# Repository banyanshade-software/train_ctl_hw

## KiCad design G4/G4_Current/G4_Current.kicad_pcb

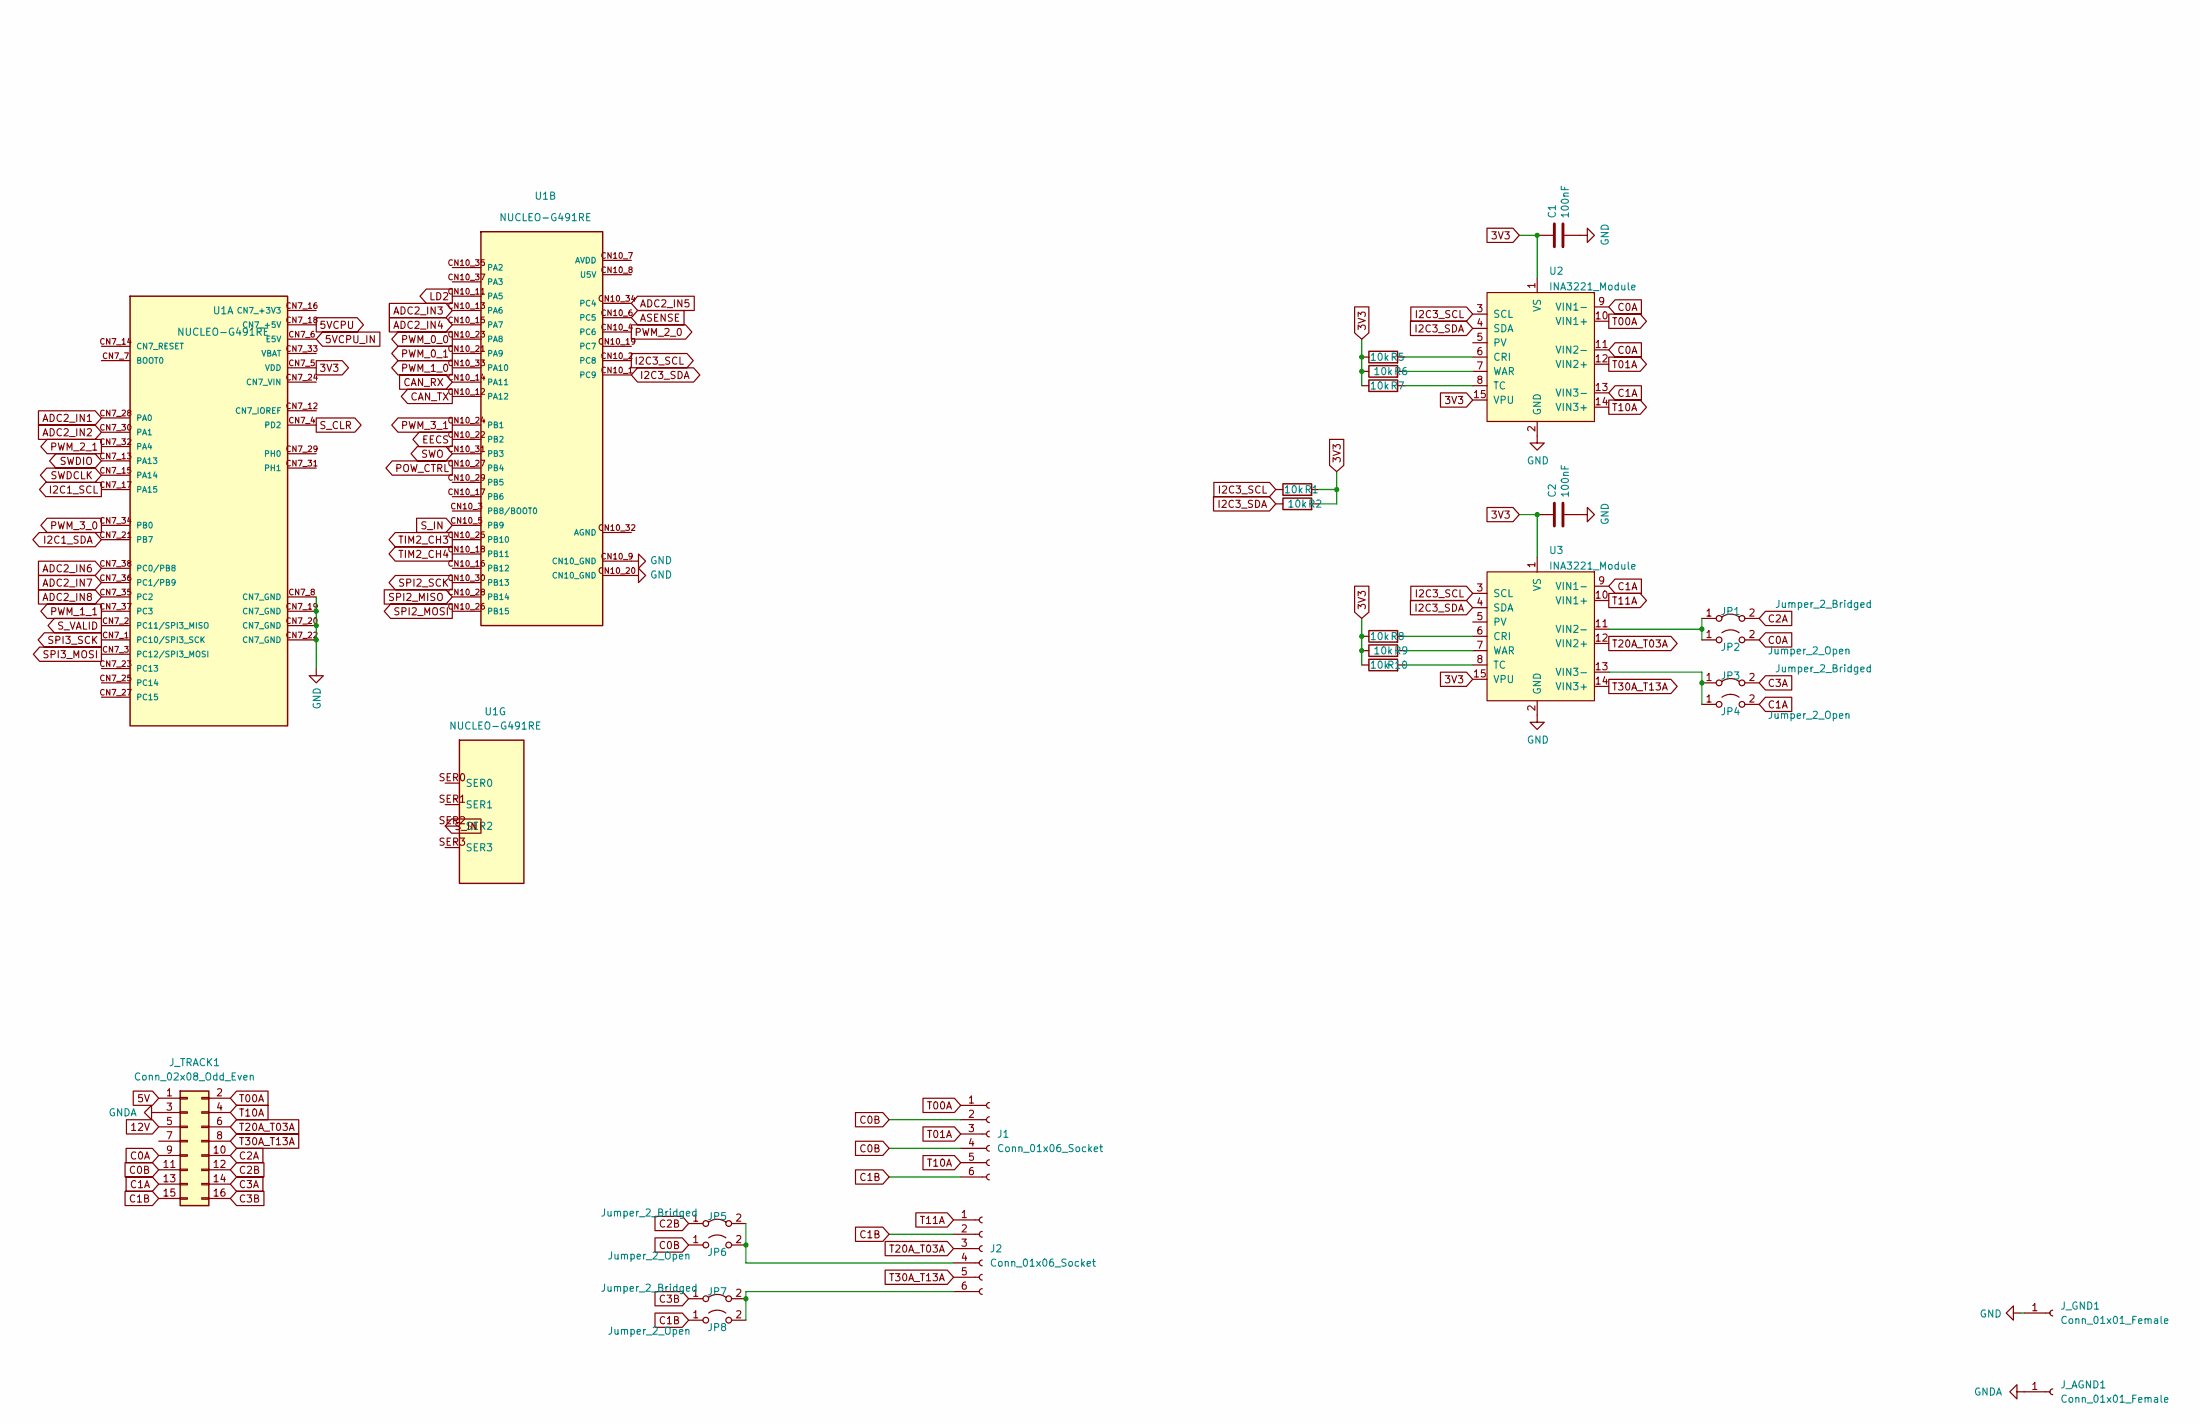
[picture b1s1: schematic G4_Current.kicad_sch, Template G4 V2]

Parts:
C1, C2: 100nF; C_Disc_D3.4mm_W2.1mm_P2.50mm
J1, J2: Conn_01x06_Socket; PinHeader_1x06_P2.54mm_Vertical
JP1, JP3, JP5, JP7: Jumper_2_Bridged; PinHeader_1x02_P2.54mm_Vertical
JP2, JP4, JP6, JP8: Jumper_2_Open; PinHeader_1x02_P2.54mm_Vertical
J_AGND1: Conn_01x01_Female; PinHeader_1x01_P2.54mm_Vertical
J_GND1: Conn_01x01_Female; PinHeader_1x01_P2.54mm_Vertical
J_TRACK1: Conn_02x08_Odd_Even; PinHeader_2x08_P2.54mm_Vertical
R1, R2, R5, R6, R7, R8, R9, R10: 10k; R_Axial_DIN0207_L6.3mm_D2.5mm_P7.62mm_Horizontal
U1: NUCLEO-G491RE; MODULE_NUCLEO-G491RE20noar; PARTREV 13
U2, U3: INA3221_Module

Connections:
3V3: C1.2, C2.2, R1.2, R2.2, R5.1, R6.1, R7.1, R8.1, R9.1, R10.1, U1.CN7_5 (VDD), U2.1 (VS), U2.15 (VPU), U3.1 (VS), U3.15 (VPU)
5V: J_TRACK1.1
5VCPU: U1.CN7_18 (CN7_+5V)
5VCPU_IN: U1.CN7_6 (E5V)
12V: J_TRACK1.5
ADC2_IN1: U1.CN7_28 (PA0)
ADC2_IN2: U1.CN7_30 (PA1)
ADC2_IN3: U1.CN10_13 (PA6)
ADC2_IN4: U1.CN10_15 (PA7)
ADC2_IN5: U1.CN10_34 (PC4)
ADC2_IN6: U1.CN7_38 (PC0/PB8)
ADC2_IN7: U1.CN7_36 (PC1/PB9)
ADC2_IN8: U1.CN7_35 (PC2)
ASENSE: U1.CN10_6 (PC5)
C0A: JP2.2 (B), J_TRACK1.9, U2.9 (VIN1-), U2.11 (VIN2-)
C0B: J1.2, J1.4, JP6.1 (A), J_TRACK1.11
C1A: JP4.2 (B), J_TRACK1.13, U2.13 (VIN3-), U3.9 (VIN1-)
C1B: J1.6, J2.2, JP8.1 (A), J_TRACK1.15
C2A: JP1.2 (B), J_TRACK1.10
C2B: JP5.1 (A), J_TRACK1.12
C3A: JP3.2 (B), J_TRACK1.14
C3B: JP7.1 (A), J_TRACK1.16
CAN_RX: U1.CN10_14 (PA11)
CAN_TX: U1.CN10_12 (PA12)
EECS: U1.CN10_22 (PB2)
GND: C1.1, C2.1, J_GND1.1, U1.CN7_8 (CN7_GND), U1.CN7_19 (CN7_GND), U1.CN7_20 (CN7_GND), U1.CN7_22 (CN7_GND), U1.CN10_9 (CN10_GND), U1.CN10_20 (CN10_GND), U2.2 (GND), U3.2 (GND)
GNDA: J_AGND1.1, J_TRACK1.3
I2C1_SCL: U1.CN7_17 (PA15)
I2C1_SDA: U1.CN7_21 (PB7)
I2C3_SCL: R1.1, U1.CN10_2 (PC8), U2.3 (SCL), U3.3 (SCL)
I2C3_SDA: R2.1, U1.CN10_1 (PC9), U2.4 (SDA), U3.4 (SDA)
LD2: U1.CN10_11 (PA5)
unnamed: J2.4, JP5.2 (B), JP6.2 (B)
unnamed: J2.6, JP7.2 (B), JP8.2 (B)
unnamed: JP1.1 (A), JP2.1 (A), U3.11 (VIN2-)
unnamed: JP3.1 (A), JP4.1 (A), U3.13 (VIN3-)
unnamed: R5.2, U2.6 (CRI)
unnamed: R7.2, U2.8 (TC)
unnamed: R6.2, U2.7 (WAR)
unnamed: R8.2, U3.6 (CRI)
unnamed: R10.2, U3.8 (TC)
unnamed: R9.2, U3.7 (WAR)
POW_CTRL: U1.CN10_27 (PB4)
PWM_0_0: U1.CN10_23 (PA8)
PWM_0_1: U1.CN10_21 (PA9)
PWM_1_0: U1.CN10_33 (PA10)
PWM_1_1: U1.CN7_37 (PC3)
PWM_2_0: U1.CN10_4 (PC6)
PWM_2_1: U1.CN7_32 (PA4)
PWM_3_0: U1.CN7_34 (PB0)
PWM_3_1: U1.CN10_24 (PB1)
SPI2_MISO: U1.CN10_28 (PB14)
SPI2_MOSI: U1.CN10_26 (PB15)
SPI2_SCK: U1.CN10_30 (PB13)
SPI3_MOSI: U1.CN7_3 (PC12/SPI3_MOSI)
SPI3_SCK: U1.CN7_1 (PC10/SPI3_SCK)
SWDCLK: U1.CN7_15 (PA14)
SWDIO: U1.CN7_13 (PA13)
SWO: U1.CN10_31 (PB3)
S_CLR: U1.CN7_4 (PD2)
S_IN: U1.CN10_5 (PB9)
S_VALID: U1.CN7_2 (PC11/SPI3_MISO)
T00A: J1.1, J_TRACK1.2, U2.10 (VIN1+)
T01A: J1.3, U2.12 (VIN2+)
T10A: J1.5, J_TRACK1.4, U2.14 (VIN3+)
T11A: J2.1, U3.10 (VIN1+)
T20A_T03A: J2.3, J_TRACK1.6, U3.12 (VIN2+)
T30A_T13A: J2.5, J_TRACK1.8, U3.14 (VIN3+)
TIM2_CH3: U1.CN10_25 (PB10)
TIM2_CH4: U1.CN10_18 (PB11)

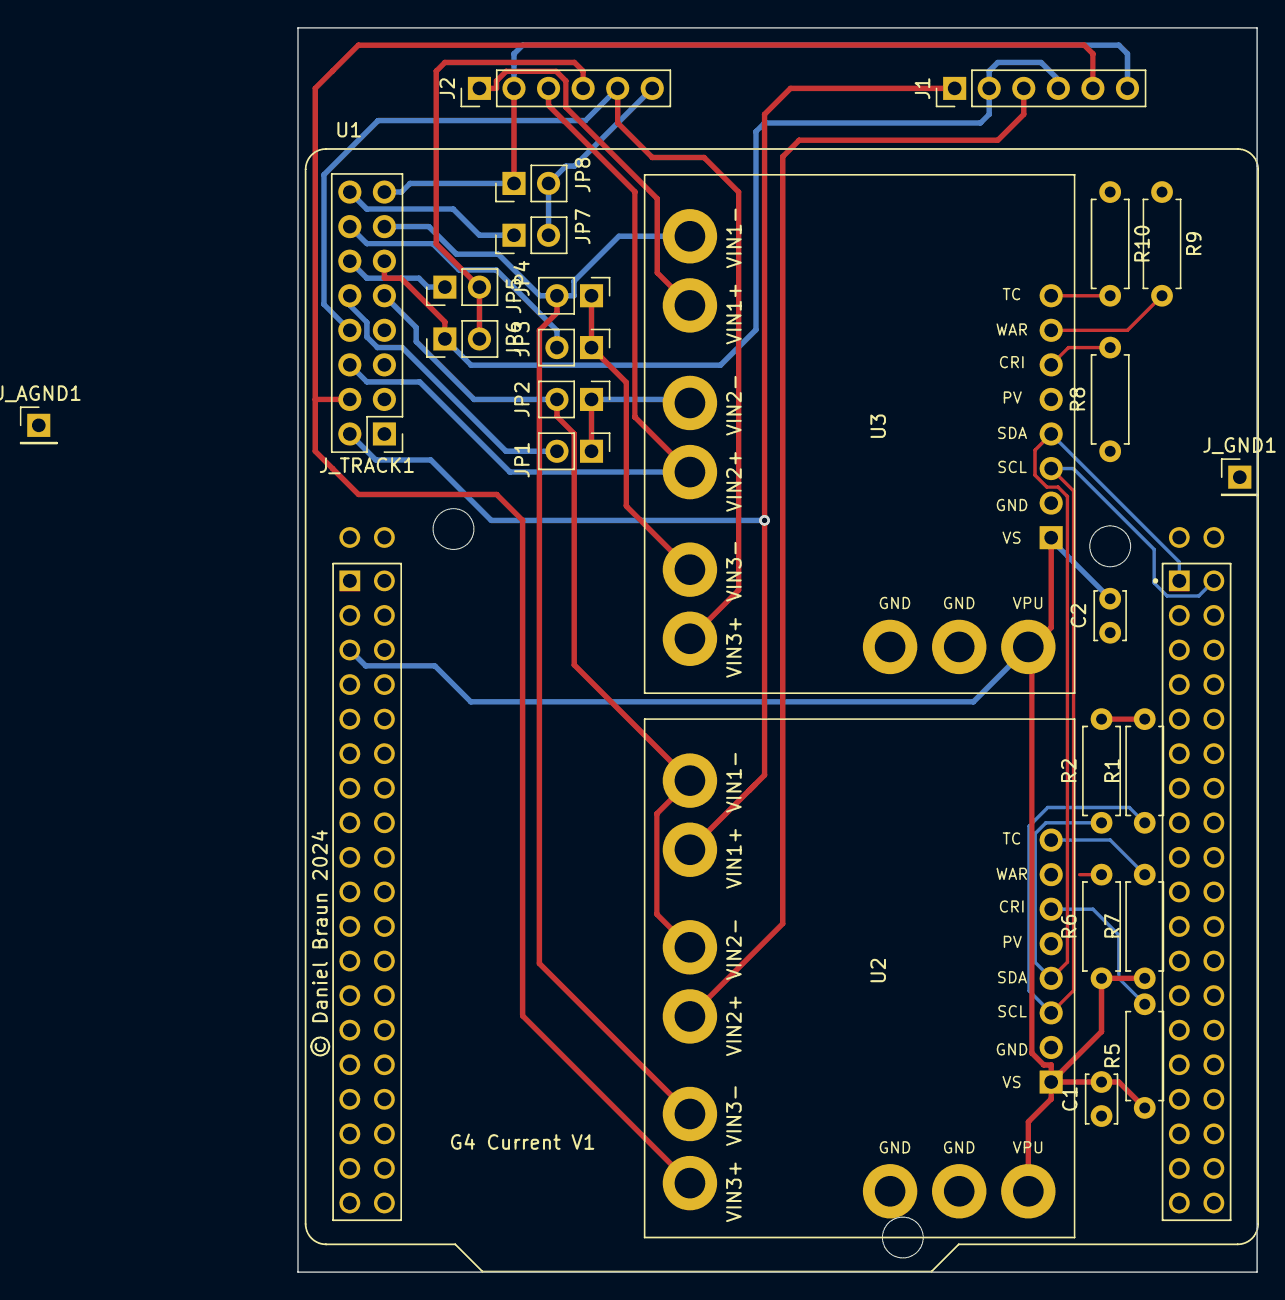
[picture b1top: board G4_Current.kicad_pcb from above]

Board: 2 copper layers, 70.5 x 91.4 mm, 26 parts (0 on the bottom side), 29 nets.

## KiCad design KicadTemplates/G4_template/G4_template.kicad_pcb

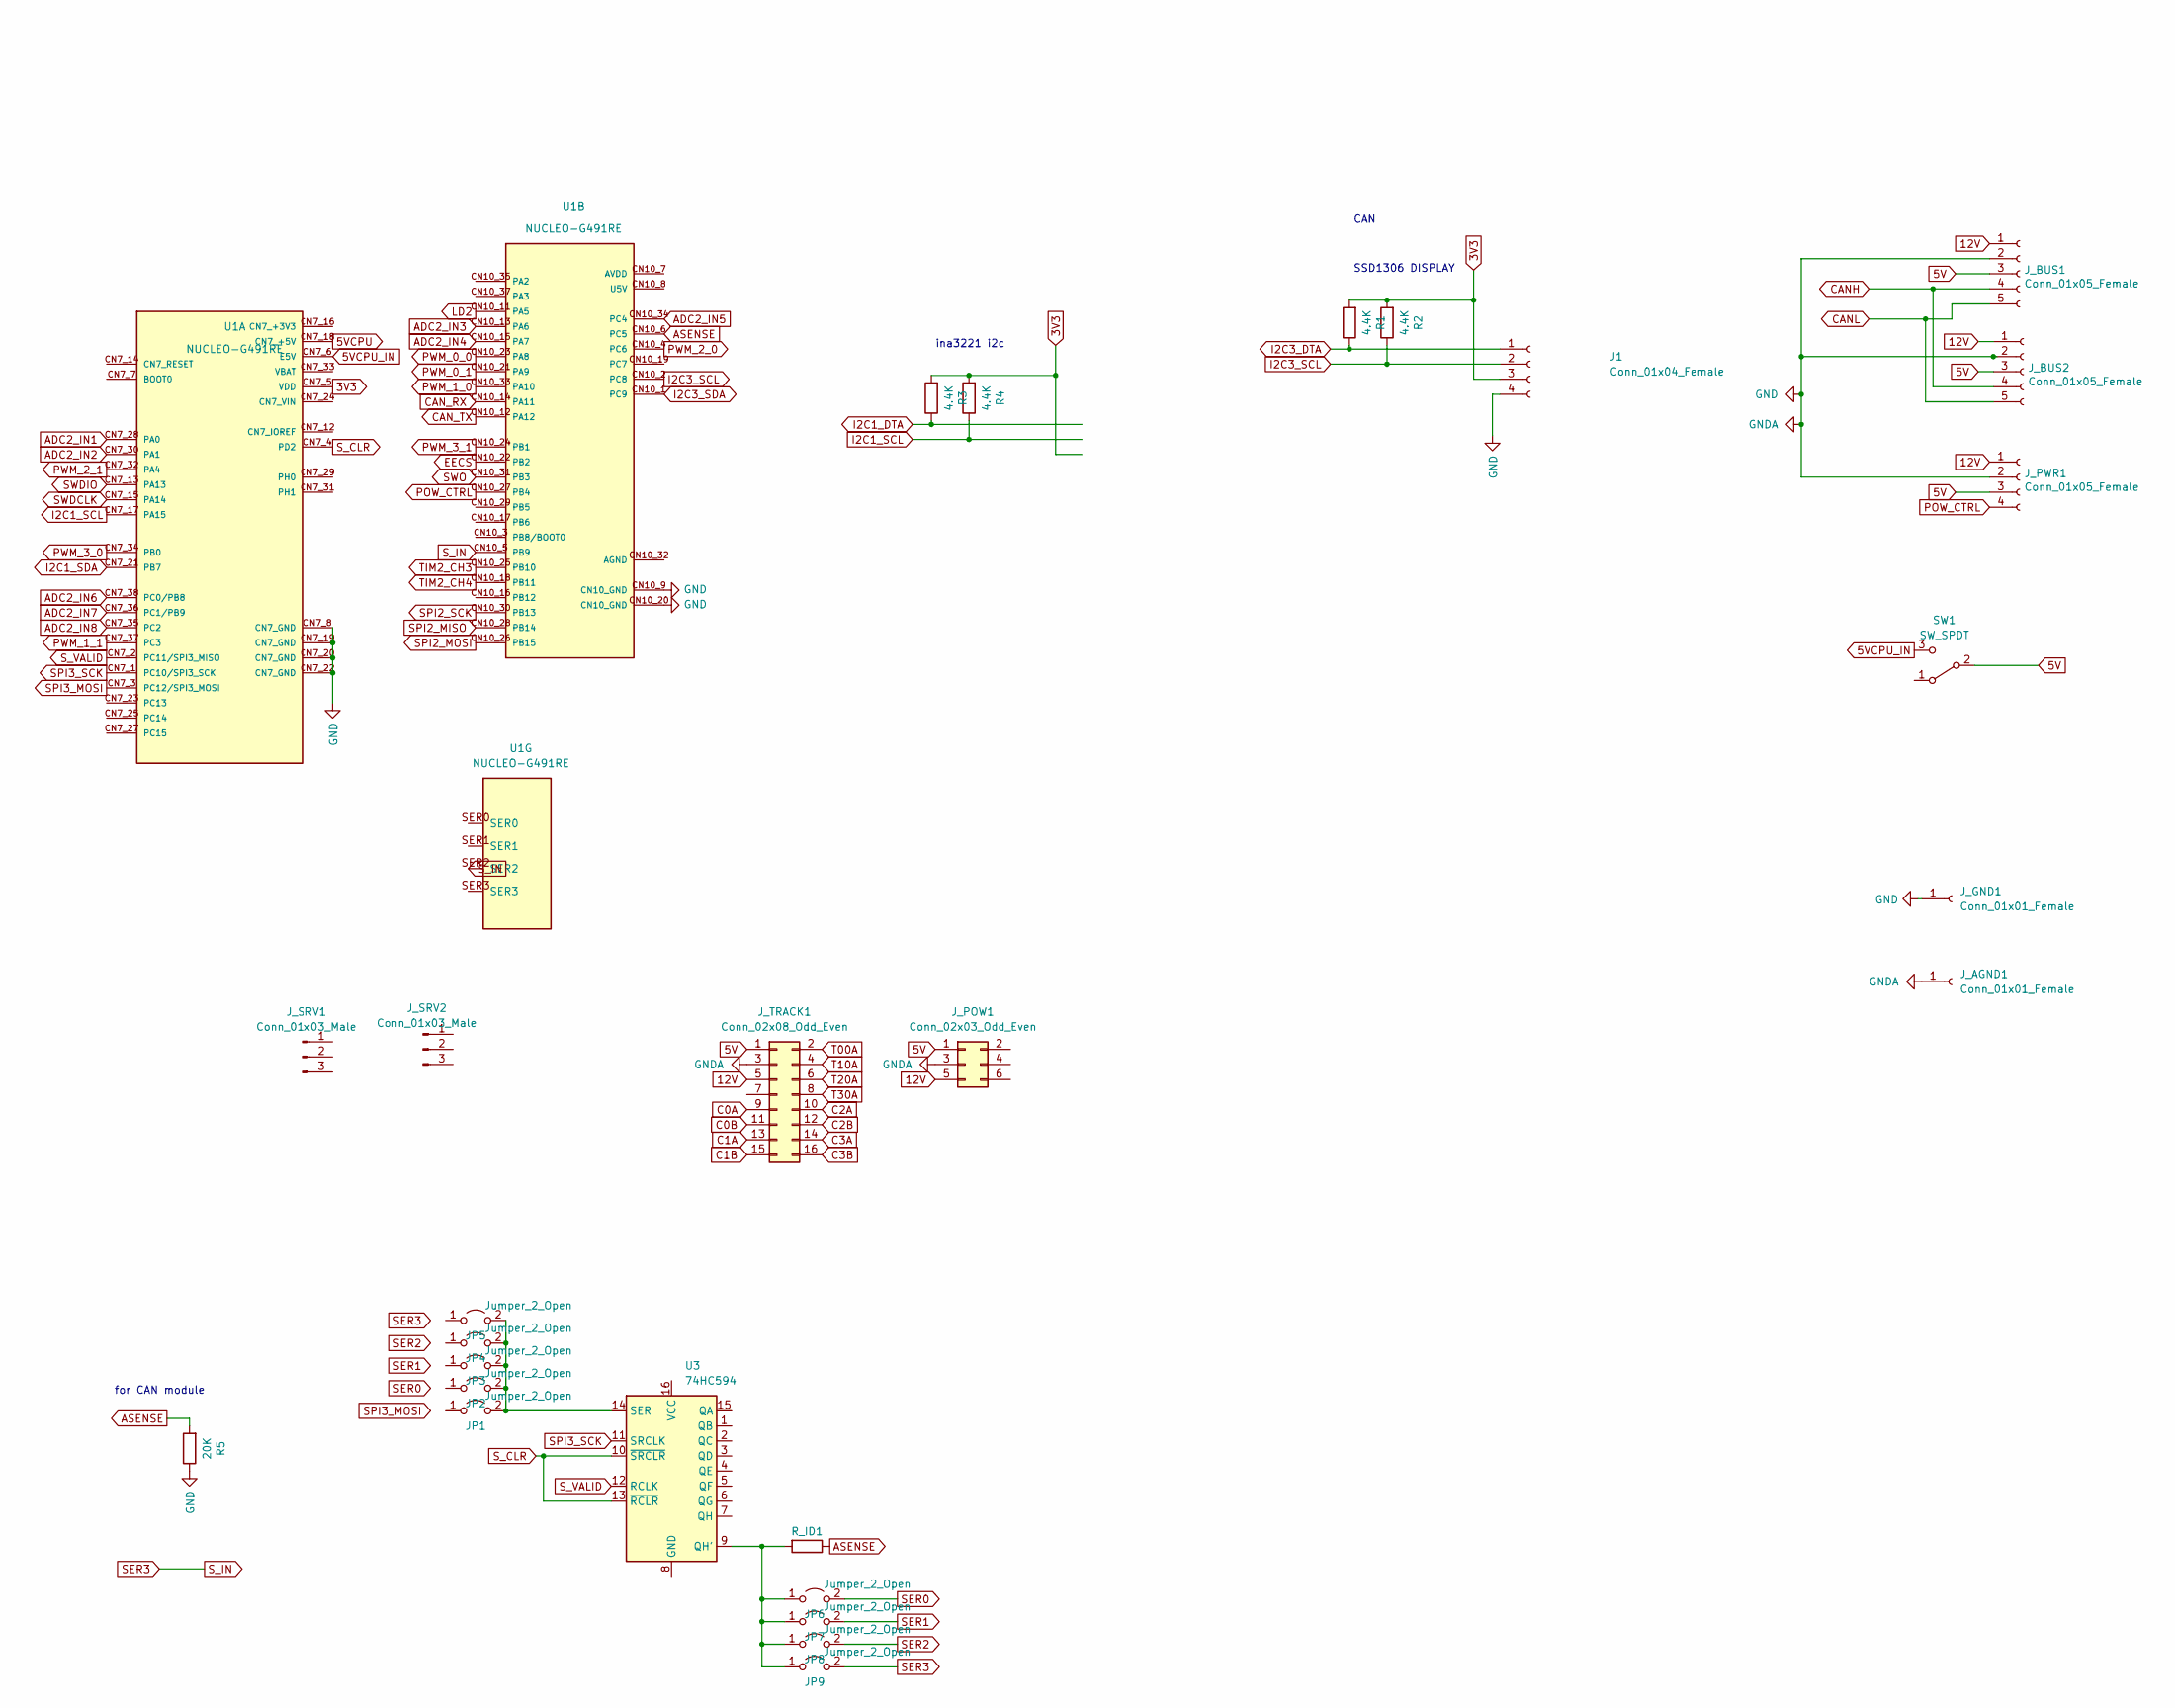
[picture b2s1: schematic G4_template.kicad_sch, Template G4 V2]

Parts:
J1: Conn_01x04_Female; PinHeader_1x04_P2.54mm_Vertical
JP1, JP2, JP3, JP4, JP5, JP6, JP7, JP8, JP9: Jumper_2_Open; PinHeader_1x02_P2.54mm_Vertical
J_AGND1: Conn_01x01_Female; PinHeader_1x01_P2.54mm_Vertical
J_BUS1, J_BUS2: Conn_01x05_Female; JST_XH_S5B-XH-A_1x05_P2.50mm_Horizontal
J_GND1: Conn_01x01_Female; PinHeader_1x01_P2.54mm_Vertical
J_POW1: Conn_02x03_Odd_Even; PinHeader_2x03_P2.54mm_Vertical
J_PWR1: Conn_01x05_Female; JST_XH_S4B-XH-A-1_1x04_P2.50mm_Horizontal
J_SRV1, J_SRV2: Conn_01x03_Male; PinHeader_1x03_P2.54mm_Horizontal
J_TRACK1: Conn_02x08_Odd_Even; PinHeader_2x08_P2.54mm_Vertical
R1, R2, R3, R4: 4.4K; R_Axial_DIN0207_L6.3mm_D2.5mm_P7.62mm_Horizontal
R5: 20K; R_Axial_DIN0207_L6.3mm_D2.5mm_P7.62mm_Horizontal
R_ID1: R_Axial_DIN0207_L6.3mm_D2.5mm_P7.62mm_Horizontal
SW1: SW_SPDT; Switch-SS12F23
U1: NUCLEO-G491RE; MODULE_NUCLEO-G491RE20; PARTREV 13
U3: 74HC594; DIP-16_W7.62mm_LongPads

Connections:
3V3: J1.3, R1.2, R2.2, R3.2, R4.2, U1.CN7_5 (VDD)
5V: J_BUS1.3, J_BUS2.3, J_POW1.1, J_PWR1.3, J_TRACK1.1, SW1.2 (B)
5VCPU: U1.CN7_18 (CN7_+5V)
5VCPU_IN: SW1.3 (C), U1.CN7_6 (E5V)
12V: J_BUS1.1, J_BUS2.1, J_POW1.5, J_PWR1.1, J_TRACK1.5
ADC2_IN1: U1.CN7_28 (PA0)
ADC2_IN2: U1.CN7_30 (PA1)
ADC2_IN3: U1.CN10_13 (PA6)
ADC2_IN4: U1.CN10_15 (PA7)
ADC2_IN5: U1.CN10_34 (PC4)
ADC2_IN6: U1.CN7_38 (PC0/PB8)
ADC2_IN7: U1.CN7_36 (PC1/PB9)
ADC2_IN8: U1.CN7_35 (PC2)
ASENSE: R5.2, R_ID1.1, U1.CN10_6 (PC5)
C0A: J_TRACK1.9
C0B: J_TRACK1.11
C1A: J_TRACK1.13
C1B: J_TRACK1.15
C2A: J_TRACK1.10
C2B: J_TRACK1.12
C3A: J_TRACK1.14
C3B: J_TRACK1.16
CANH: J_BUS1.4, J_BUS2.4
CANL: J_BUS1.5, J_BUS2.5
CAN_RX: U1.CN10_14 (PA11)
CAN_TX: U1.CN10_12 (PA12)
EECS: U1.CN10_22 (PB2)
GND: J1.4, J_AGND1.1, J_BUS1.2, J_BUS2.2, J_GND1.1, J_POW1.3, J_PWR1.2, J_TRACK1.3, R5.1, U1.CN7_8 (CN7_GND), U1.CN7_19 (CN7_GND), U1.CN7_20 (CN7_GND), U1.CN7_22 (CN7_GND), U1.CN10_9 (CN10_GND), U1.CN10_20 (CN10_GND)
I2C1_DTA: R3.1
I2C1_SCL: R4.1, U1.CN7_17 (PA15)
I2C1_SDA: U1.CN7_21 (PB7)
I2C3_DTA: J1.1, R1.1
I2C3_SCL: J1.2, R2.1, U1.CN10_2 (PC8)
I2C3_SDA: U1.CN10_1 (PC9)
LD2: U1.CN10_11 (PA5)
unnamed: JP1.2 (B), JP2.2 (B), JP3.2 (B), JP4.2 (B), JP5.2 (B), U3.14 (SER)
unnamed: JP6.1 (A), JP7.1 (A), JP8.1 (A), JP9.1 (A), R_ID1.2, U3.9 (QH')
POW_CTRL: J_PWR1.4, U1.CN10_27 (PB4)
PWM_0_0: U1.CN10_23 (PA8)
PWM_0_1: U1.CN10_21 (PA9)
PWM_1_0: U1.CN10_33 (PA10)
PWM_1_1: U1.CN7_37 (PC3)
PWM_2_0: U1.CN10_4 (PC6)
PWM_2_1: U1.CN7_32 (PA4)
PWM_3_0: U1.CN7_34 (PB0)
PWM_3_1: U1.CN10_24 (PB1)
SER0: JP6.2 (B)
SER1: JP7.2 (B)
SER2: JP8.2 (B)
SER3: JP9.2 (B), U1.CN10_5 (PB9)
SPI2_MISO: U1.CN10_28 (PB14)
SPI2_MOSI: U1.CN10_26 (PB15)
SPI2_SCK: U1.CN10_30 (PB13)
SPI3_MOSI: U1.CN7_3 (PC12/SPI3_MOSI)
SPI3_SCK: U1.CN7_1 (PC10/SPI3_SCK), U3.11 (SRCLK)
SWDCLK: U1.CN7_15 (PA14)
SWDIO: U1.CN7_13 (PA13)
SWO: U1.CN10_31 (PB3)
S_CLR: U1.CN7_4 (PD2), U3.10 (~SRCLR), U3.13 (~RCLR)
S_VALID: U1.CN7_2 (PC11/SPI3_MISO), U3.12 (RCLK)
T00A: J_TRACK1.2
T10A: J_TRACK1.4
T20A: J_TRACK1.6
T30A: J_TRACK1.8
TIM2_CH3: U1.CN10_25 (PB10)
TIM2_CH4: U1.CN10_18 (PB11)

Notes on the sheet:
SSD1306 DISPLAY
for CAN module
CAN
ina3221 i2c

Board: 2 copper layers, 28 parts (0 on the bottom side), 18 nets, no tracks yet.

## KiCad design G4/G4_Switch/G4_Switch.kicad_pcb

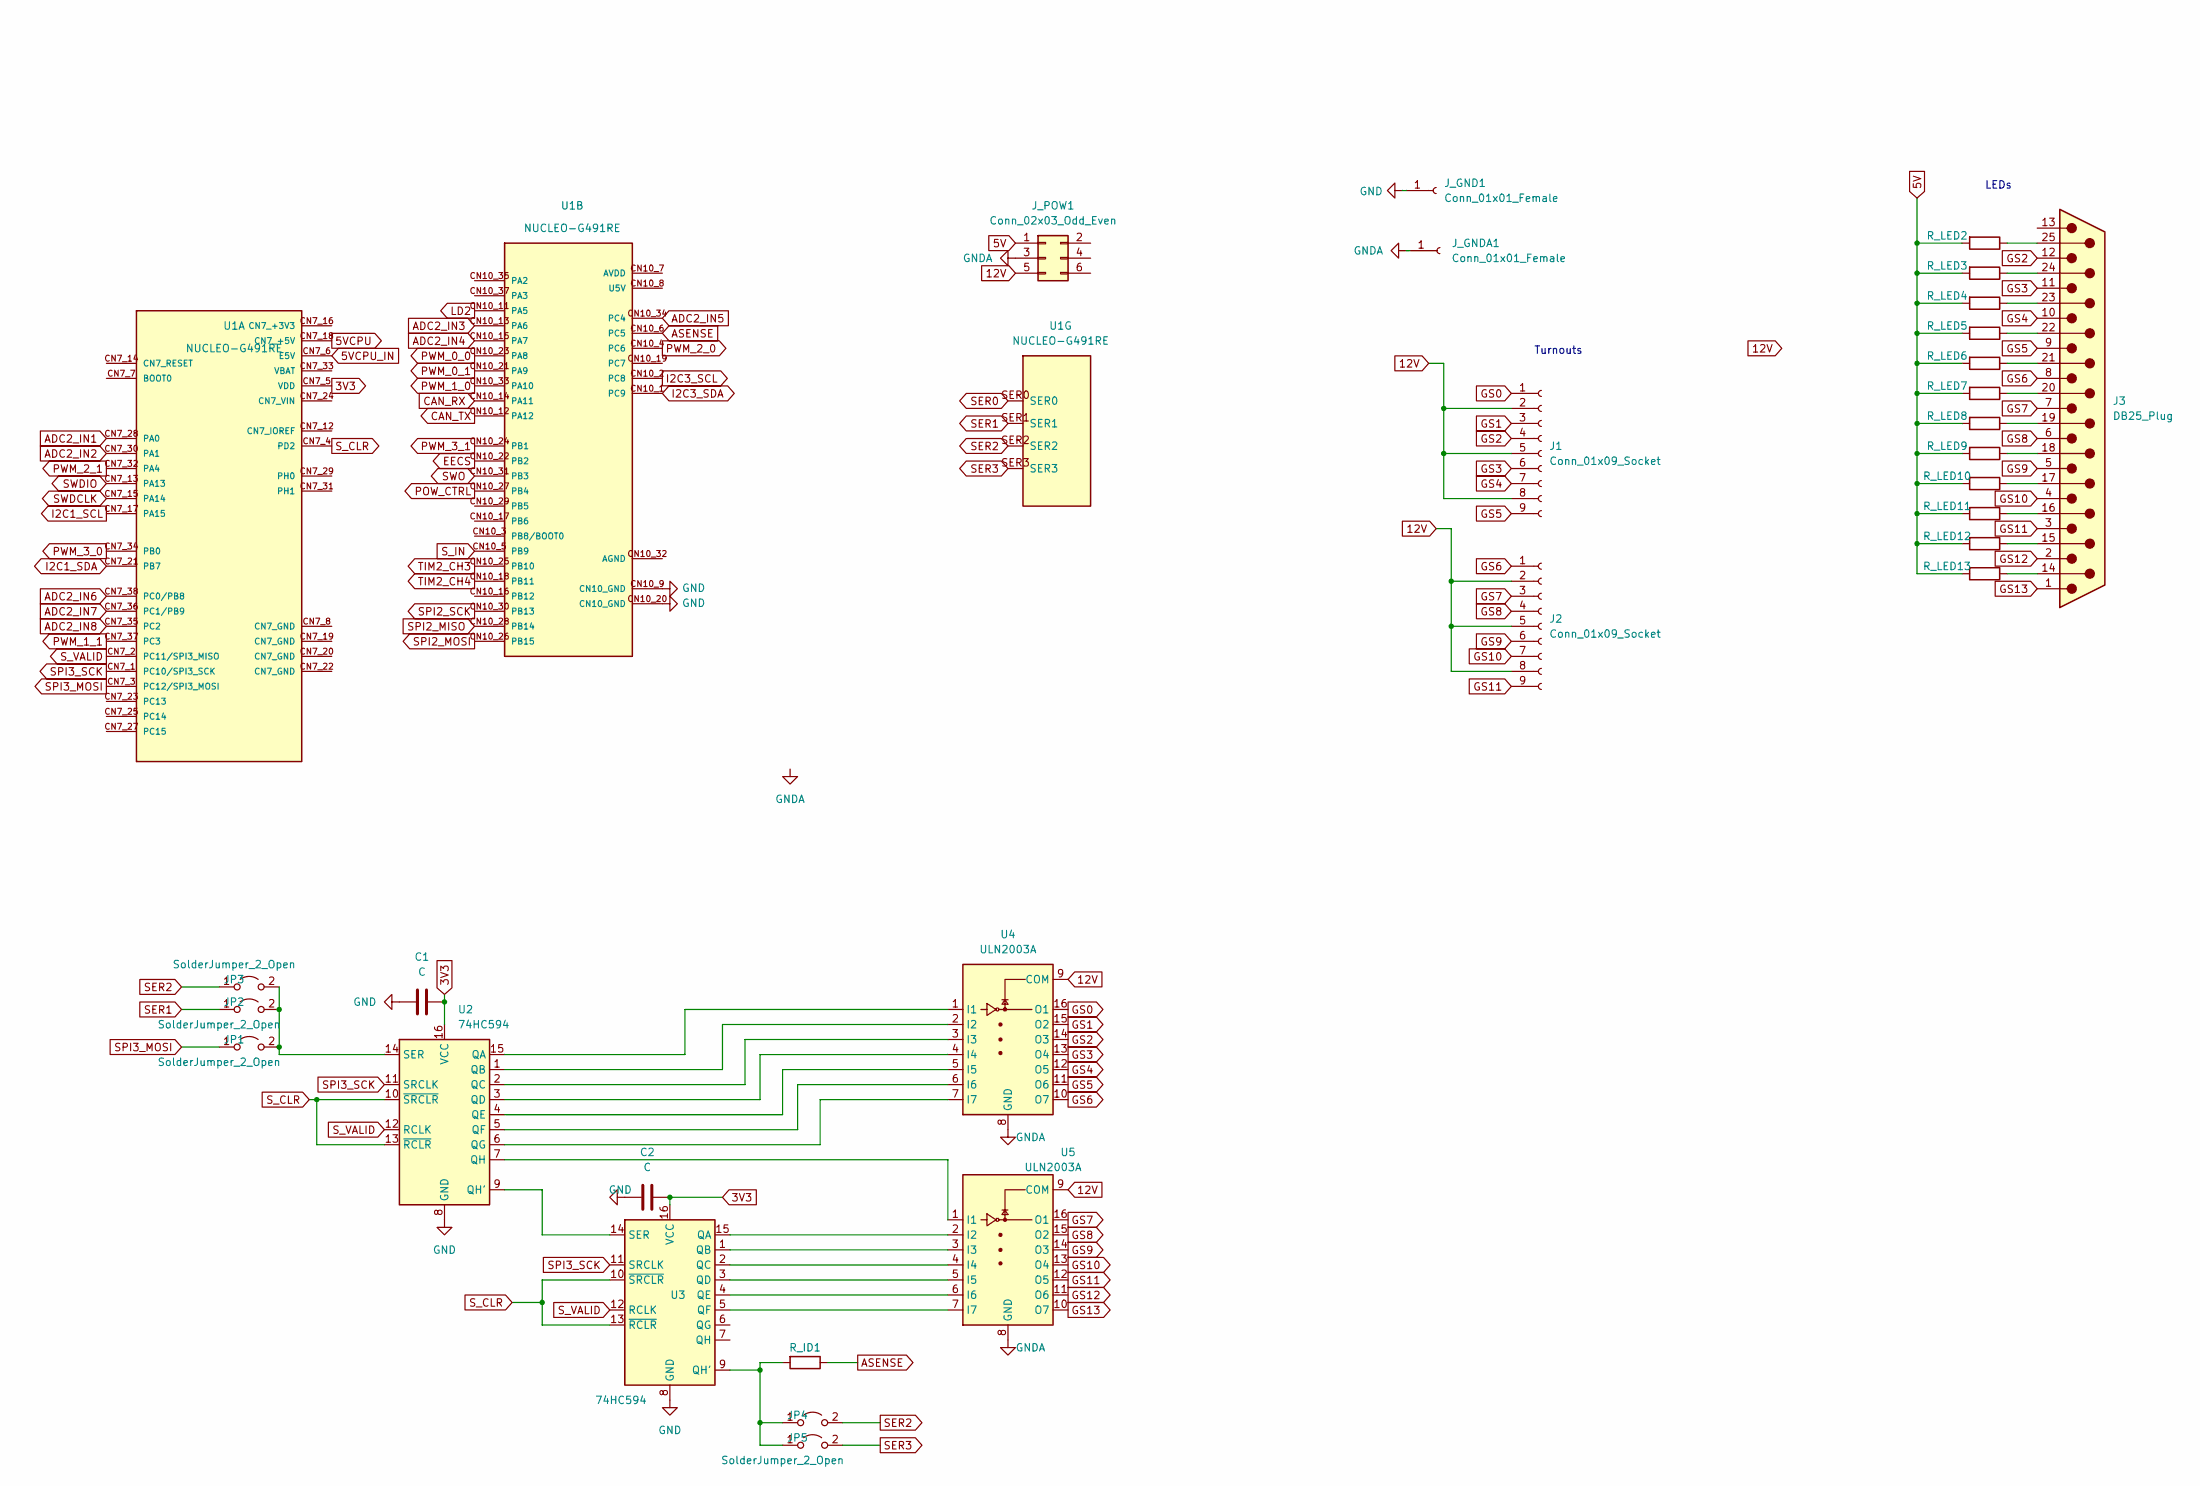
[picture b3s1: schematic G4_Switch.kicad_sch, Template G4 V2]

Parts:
C1, C2: C; C_Disc_D3.4mm_W2.1mm_P2.50mm
J1, J2: Conn_01x09_Socket; PinHeader_1x09_P2.54mm_Vertical
J3: DB25_Plug; DSUB-25_Female_Horizontal_P2.77x2.84mm_EdgePinOffset7.70mm_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
JP1, JP2, JP3, JP4, JP5: SolderJumper_2_Open; PinHeader_1x02_P2.54mm_Vertical
J_GND1: Conn_01x01_Female; PinHeader_1x01_P2.54mm_Vertical
J_GNDA1: Conn_01x01_Female; PinHeader_1x01_P2.54mm_Vertical
J_POW1: Conn_02x03_Odd_Even; PinHeader_2x03_P2.54mm_Vertical
R_ID1: R_Axial_DIN0207_L6.3mm_D2.5mm_P7.62mm_Horizontal
R_LED2, R_LED3, R_LED4, R_LED5, R_LED6, R_LED7, R_LED8, R_LED9, R_LED10, R_LED11, R_LED12, R_LED13: R_Axial_DIN0207_L6.3mm_D2.5mm_P7.62mm_Horizontal
U1: NUCLEO-G491RE; MODULE_NUCLEO-G491RE20noar; PARTREV 13
U2, U3: 74HC594; DIP-16_W7.62mm_LongPads
U4, U5: ULN2003A; DIP-16_W7.62mm

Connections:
3V3: C1.2, C2.2, U1.CN7_5 (VDD), U2.16 (VCC), U3.16 (VCC)
5V: J_POW1.1, R_LED2.2, R_LED3.2, R_LED4.2, R_LED5.2, R_LED6.2, R_LED7.2, R_LED8.2, R_LED9.2, R_LED10.2, R_LED11.2, R_LED12.2, R_LED13.2
5VCPU: U1.CN7_18 (CN7_+5V)
5VCPU_IN: U1.CN7_6 (E5V)
12V: J1.2, J1.5, J1.8, J2.2, J2.5, J2.8, J_POW1.5, U4.9 (COM), U5.9 (COM)
ADC2_IN1: U1.CN7_28 (PA0)
ADC2_IN2: U1.CN7_30 (PA1)
ADC2_IN3: U1.CN10_13 (PA6)
ADC2_IN4: U1.CN10_15 (PA7)
ADC2_IN5: U1.CN10_34 (PC4)
ADC2_IN6: U1.CN7_38 (PC0/PB8)
ADC2_IN7: U1.CN7_36 (PC1/PB9)
ADC2_IN8: U1.CN7_35 (PC2)
ASENSE: R_ID1.1, U1.CN10_6 (PC5)
CAN_RX: U1.CN10_14 (PA11)
CAN_TX: U1.CN10_12 (PA12)
EECS: U1.CN10_22 (PB2)
GND: C1.1, C2.1, J_GND1.1, U1.CN10_9 (CN10_GND), U1.CN10_20 (CN10_GND), U2.8 (GND), U3.8 (GND)
GNDA: J_GNDA1.1, J_POW1.3, U4.8 (GND), U5.8 (GND)
GS0: J1.1, U4.16 (O1)
GS1: J1.3, U4.15 (O2)
GS2: J1.4, J3.12, U4.14 (O3)
GS3: J1.6, J3.11, U4.13 (O4)
GS4: J1.7, J3.10, U4.12 (O5)
GS5: J1.9, J3.9, U4.11 (O6)
GS6: J2.1, J3.8, U4.10 (O7)
GS7: J2.3, J3.7, U5.16 (O1)
GS8: J2.4, J3.6, U5.15 (O2)
GS9: J2.6, J3.5, U5.14 (O3)
GS10: J2.7, J3.4, U5.13 (O4)
GS11: J2.9, J3.3, U5.12 (O5)
GS12: J3.2, U5.11 (O6)
GS13: J3.1, U5.10 (O7)
I2C1_SCL: U1.CN7_17 (PA15)
I2C1_SDA: U1.CN7_21 (PB7)
I2C3_SCL: U1.CN10_2 (PC8)
I2C3_SDA: U1.CN10_1 (PC9)
LD2: U1.CN10_11 (PA5)
unnamed: J3.14, R_LED13.1
unnamed: J3.15, R_LED12.1
unnamed: J3.16, R_LED11.1
unnamed: J3.17, R_LED10.1
unnamed: J3.18, R_LED9.1
unnamed: J3.19, R_LED8.1
unnamed: J3.20, R_LED7.1
unnamed: J3.21, R_LED6.1
unnamed: J3.22, R_LED5.1
unnamed: J3.23, R_LED4.1
unnamed: J3.24, R_LED3.1
unnamed: J3.25, R_LED2.1
unnamed: JP1.2 (B), JP2.2 (B), JP3.2 (B), U2.14 (SER)
unnamed: JP4.1 (A), JP5.1 (A), R_ID1.2, U3.9 (QH')
unnamed: U2.15 (QA), U4.1 (I1)
unnamed: U2.1 (QB), U4.2 (I2)
unnamed: U2.2 (QC), U4.3 (I3)
unnamed: U2.3 (QD), U4.4 (I4)
unnamed: U2.4 (QE), U4.5 (I5)
unnamed: U2.5 (QF), U4.6 (I6)
unnamed: U2.6 (QG), U4.7 (I7)
unnamed: U2.9 (QH'), U3.14 (SER)
unnamed: U2.7 (QH), U5.1 (I1)
unnamed: U3.15 (QA), U5.2 (I2)
unnamed: U3.1 (QB), U5.3 (I3)
unnamed: U3.2 (QC), U5.4 (I4)
unnamed: U3.3 (QD), U5.5 (I5)
unnamed: U3.4 (QE), U5.6 (I6)
unnamed: U3.5 (QF), U5.7 (I7)
POW_CTRL: U1.CN10_27 (PB4)
PWM_0_0: U1.CN10_23 (PA8)
PWM_0_1: U1.CN10_21 (PA9)
PWM_1_0: U1.CN10_33 (PA10)
PWM_1_1: U1.CN7_37 (PC3)
PWM_2_0: U1.CN10_4 (PC6)
PWM_2_1: U1.CN7_32 (PA4)
PWM_3_0: U1.CN7_34 (PB0)
PWM_3_1: U1.CN10_24 (PB1)
SER0: U1.SER0
SER1: JP2.1 (A), U1.SER1
SER2: JP3.1 (A), JP4.2 (B), U1.SER2
SER3: JP5.2 (B), U1.SER3
SPI2_MISO: U1.CN10_28 (PB14)
SPI2_MOSI: U1.CN10_26 (PB15)
SPI2_SCK: U1.CN10_30 (PB13)
SPI3_MOSI: JP1.1 (A), U1.CN7_3 (PC12/SPI3_MOSI)
SPI3_SCK: U1.CN7_1 (PC10/SPI3_SCK), U2.11 (SRCLK), U3.11 (SRCLK)
SWDCLK: U1.CN7_15 (PA14)
SWDIO: U1.CN7_13 (PA13)
SWO: U1.CN10_31 (PB3)
S_CLR: U1.CN7_4 (PD2), U2.10 (~SRCLR), U2.13 (~RCLR), U3.10 (~SRCLR), U3.13 (~RCLR)
S_IN: U1.CN10_5 (PB9)
S_VALID: U1.CN7_2 (PC11/SPI3_MISO), U2.12 (RCLK), U3.12 (RCLK)
TIM2_CH3: U1.CN10_25 (PB10)
TIM2_CH4: U1.CN10_18 (PB11)

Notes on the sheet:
Turnouts
LEDs

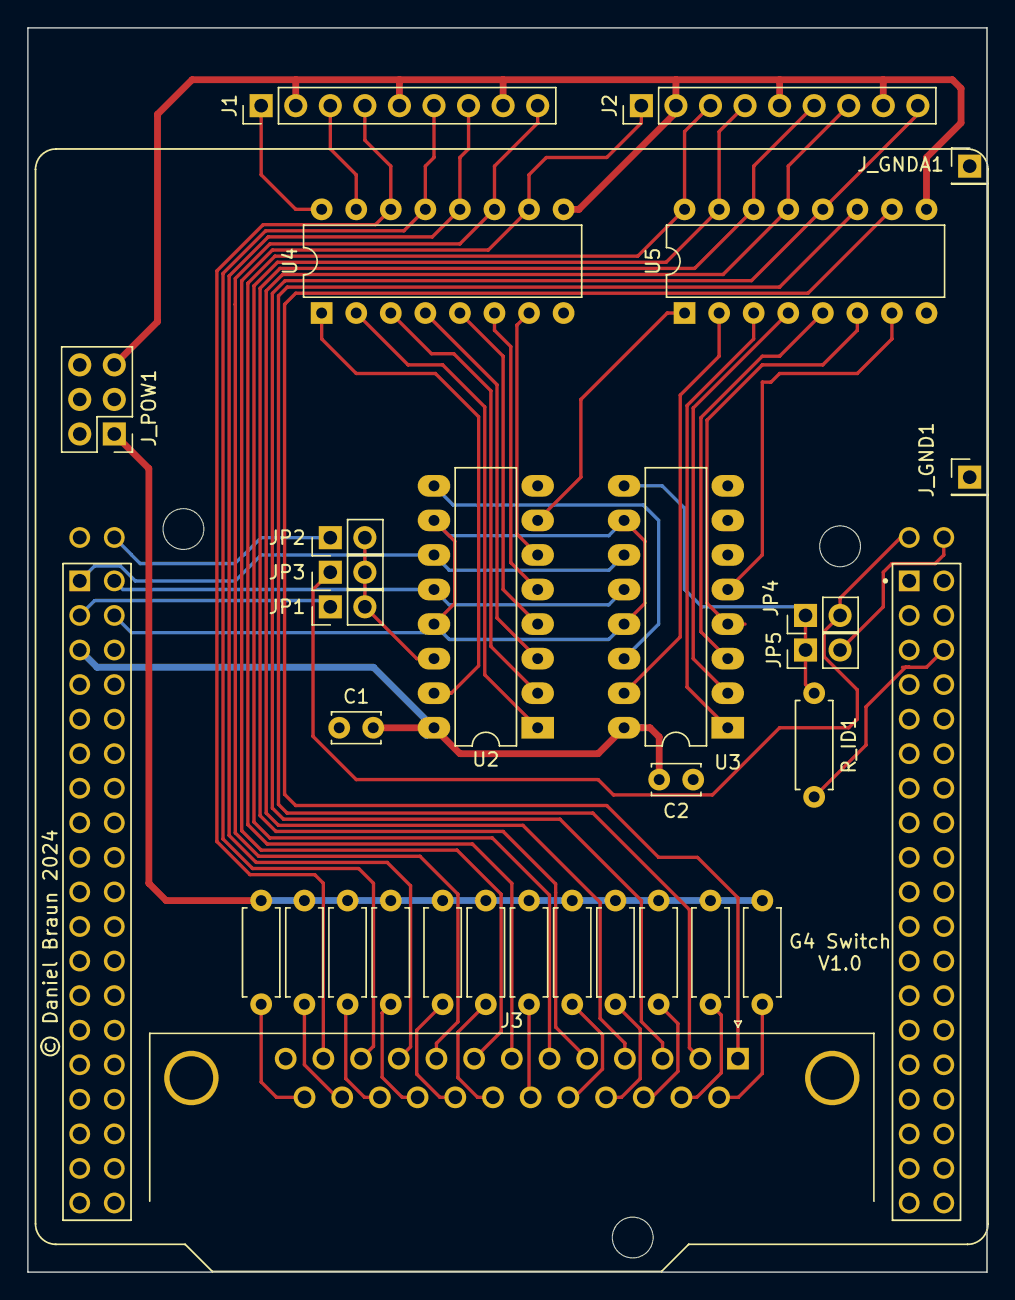
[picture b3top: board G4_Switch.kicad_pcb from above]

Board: 2 copper layers, 70.5 x 91.4 mm, 31 parts (0 on the bottom side), 56 nets.

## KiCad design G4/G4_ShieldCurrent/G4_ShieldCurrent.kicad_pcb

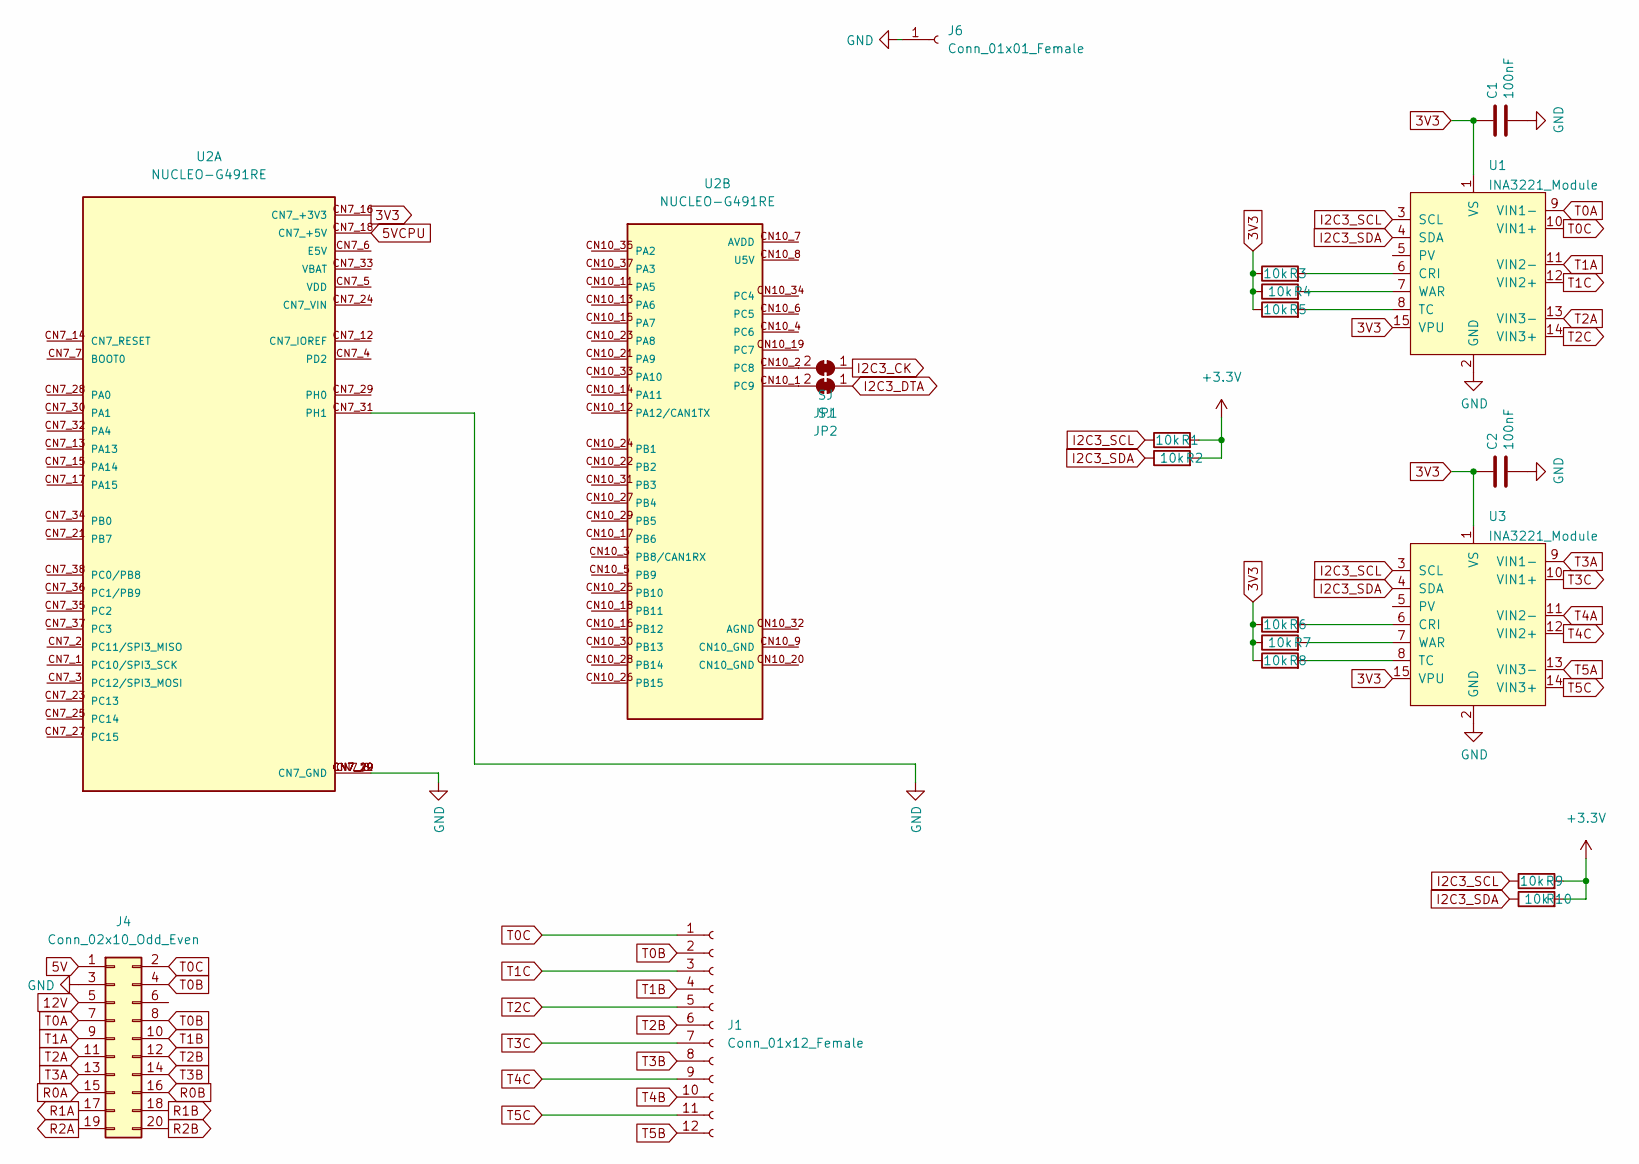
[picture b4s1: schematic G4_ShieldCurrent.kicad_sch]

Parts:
C1, C2: 100nF; C_Disc_D3.4mm_W2.1mm_P2.50mm
J1: Conn_01x12_Female; JST_XA_S12B-XASK-1N-BN_1x12_P2.50mm_Horizontal
J4: Conn_02x10_Odd_Even; PinHeader_2x10_P2.54mm_Vertical
J6: Conn_01x01_Female; PinHeader_1x01_P2.54mm_Vertical
JP1, JP2: SJ; PinHeader_1x02_P2.54mm_Vertical
R1, R2, R3, R4, R5, R6, R7, R8, R9, R10: 10k; R_Axial_DIN0207_L6.3mm_D2.5mm_P7.62mm_Horizontal
U1, U3: INA3221_Module
U2: NUCLEO-G491RE; MODULE_NUCLEO-G491RE20; PARTREV 13

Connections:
3V3: C1.2, C2.2, R3.1, R4.1, R5.1, R6.1, R7.1, R8.1, U1.1 (VS), U1.15 (VPU), U2.CN7_16 (CN7_+3V3), U3.1 (VS), U3.15 (VPU)
5V: J4.1
5VCPU: U2.CN7_18 (CN7_+5V)
12V: J4.5
+3V3: R1.2, R2.2, R9.2, R10.2
GND: C1.1, C2.1, J4.3, J6.1, U1.2 (GND), U2.CN7_8 (CN7_GND), U2.CN7_19 (CN7_GND), U2.CN7_20 (CN7_GND), U2.CN7_22 (CN7_GND), U2.CN7_31 (PH1), U3.2 (GND)
I2C3_CK: JP1.1 (A)
I2C3_DTA: JP2.1 (A)
I2C3_SCL: R1.1, R9.1, U1.3 (SCL), U3.3 (SCL)
I2C3_SDA: R2.1, R10.1, U1.4 (SDA), U3.4 (SDA)
unnamed: JP1.2 (B), U2.CN10_2 (PC8)
unnamed: JP2.2 (B), U2.CN10_1 (PC9)
unnamed: R3.2, U1.6 (CRI)
unnamed: R4.2, U1.7 (WAR)
unnamed: R5.2, U1.8 (TC)
unnamed: R6.2, U3.6 (CRI)
unnamed: R7.2, U3.7 (WAR)
unnamed: R8.2, U3.8 (TC)
R0A: J4.15
R0B: J4.16
R1A: J4.17
R1B: J4.18
R2A: J4.19
R2B: J4.20
T0A: J4.7, U1.9 (VIN1-)
T0B: J1.2, J4.4, J4.8
T0C: J1.1, J4.2, U1.10 (VIN1+)
T1A: J4.9, U1.11 (VIN2-)
T1B: J1.4, J4.10
T1C: J1.3, U1.12 (VIN2+)
T2A: J4.11, U1.13 (VIN3-)
T2B: J1.6, J4.12
T2C: J1.5, U1.14 (VIN3+)
T3A: J4.13, U3.9 (VIN1-)
T3B: J1.8, J4.14
T3C: J1.7, U3.10 (VIN1+)
T4A: U3.11 (VIN2-)
T4B: J1.10
T4C: J1.9, U3.12 (VIN2+)
T5A: U3.13 (VIN3-)
T5B: J1.12
T5C: J1.11, U3.14 (VIN3+)

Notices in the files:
G4/G4_Current/G4_Current.kicad_pcb:
© Daniel Braun 2024
G4/G4_ShieldCurrent/G4_ShieldCurrent.kicad_pcb:
© Daniel Braun 2023
Mainboard4/CurrentDetect4/CurrentDetect4.kicad_pcb:
© Daniel Braun 2022
Mainboard4/Mainboard4/Mainboard4.kicad_pcb:
© D. Braun 2022
